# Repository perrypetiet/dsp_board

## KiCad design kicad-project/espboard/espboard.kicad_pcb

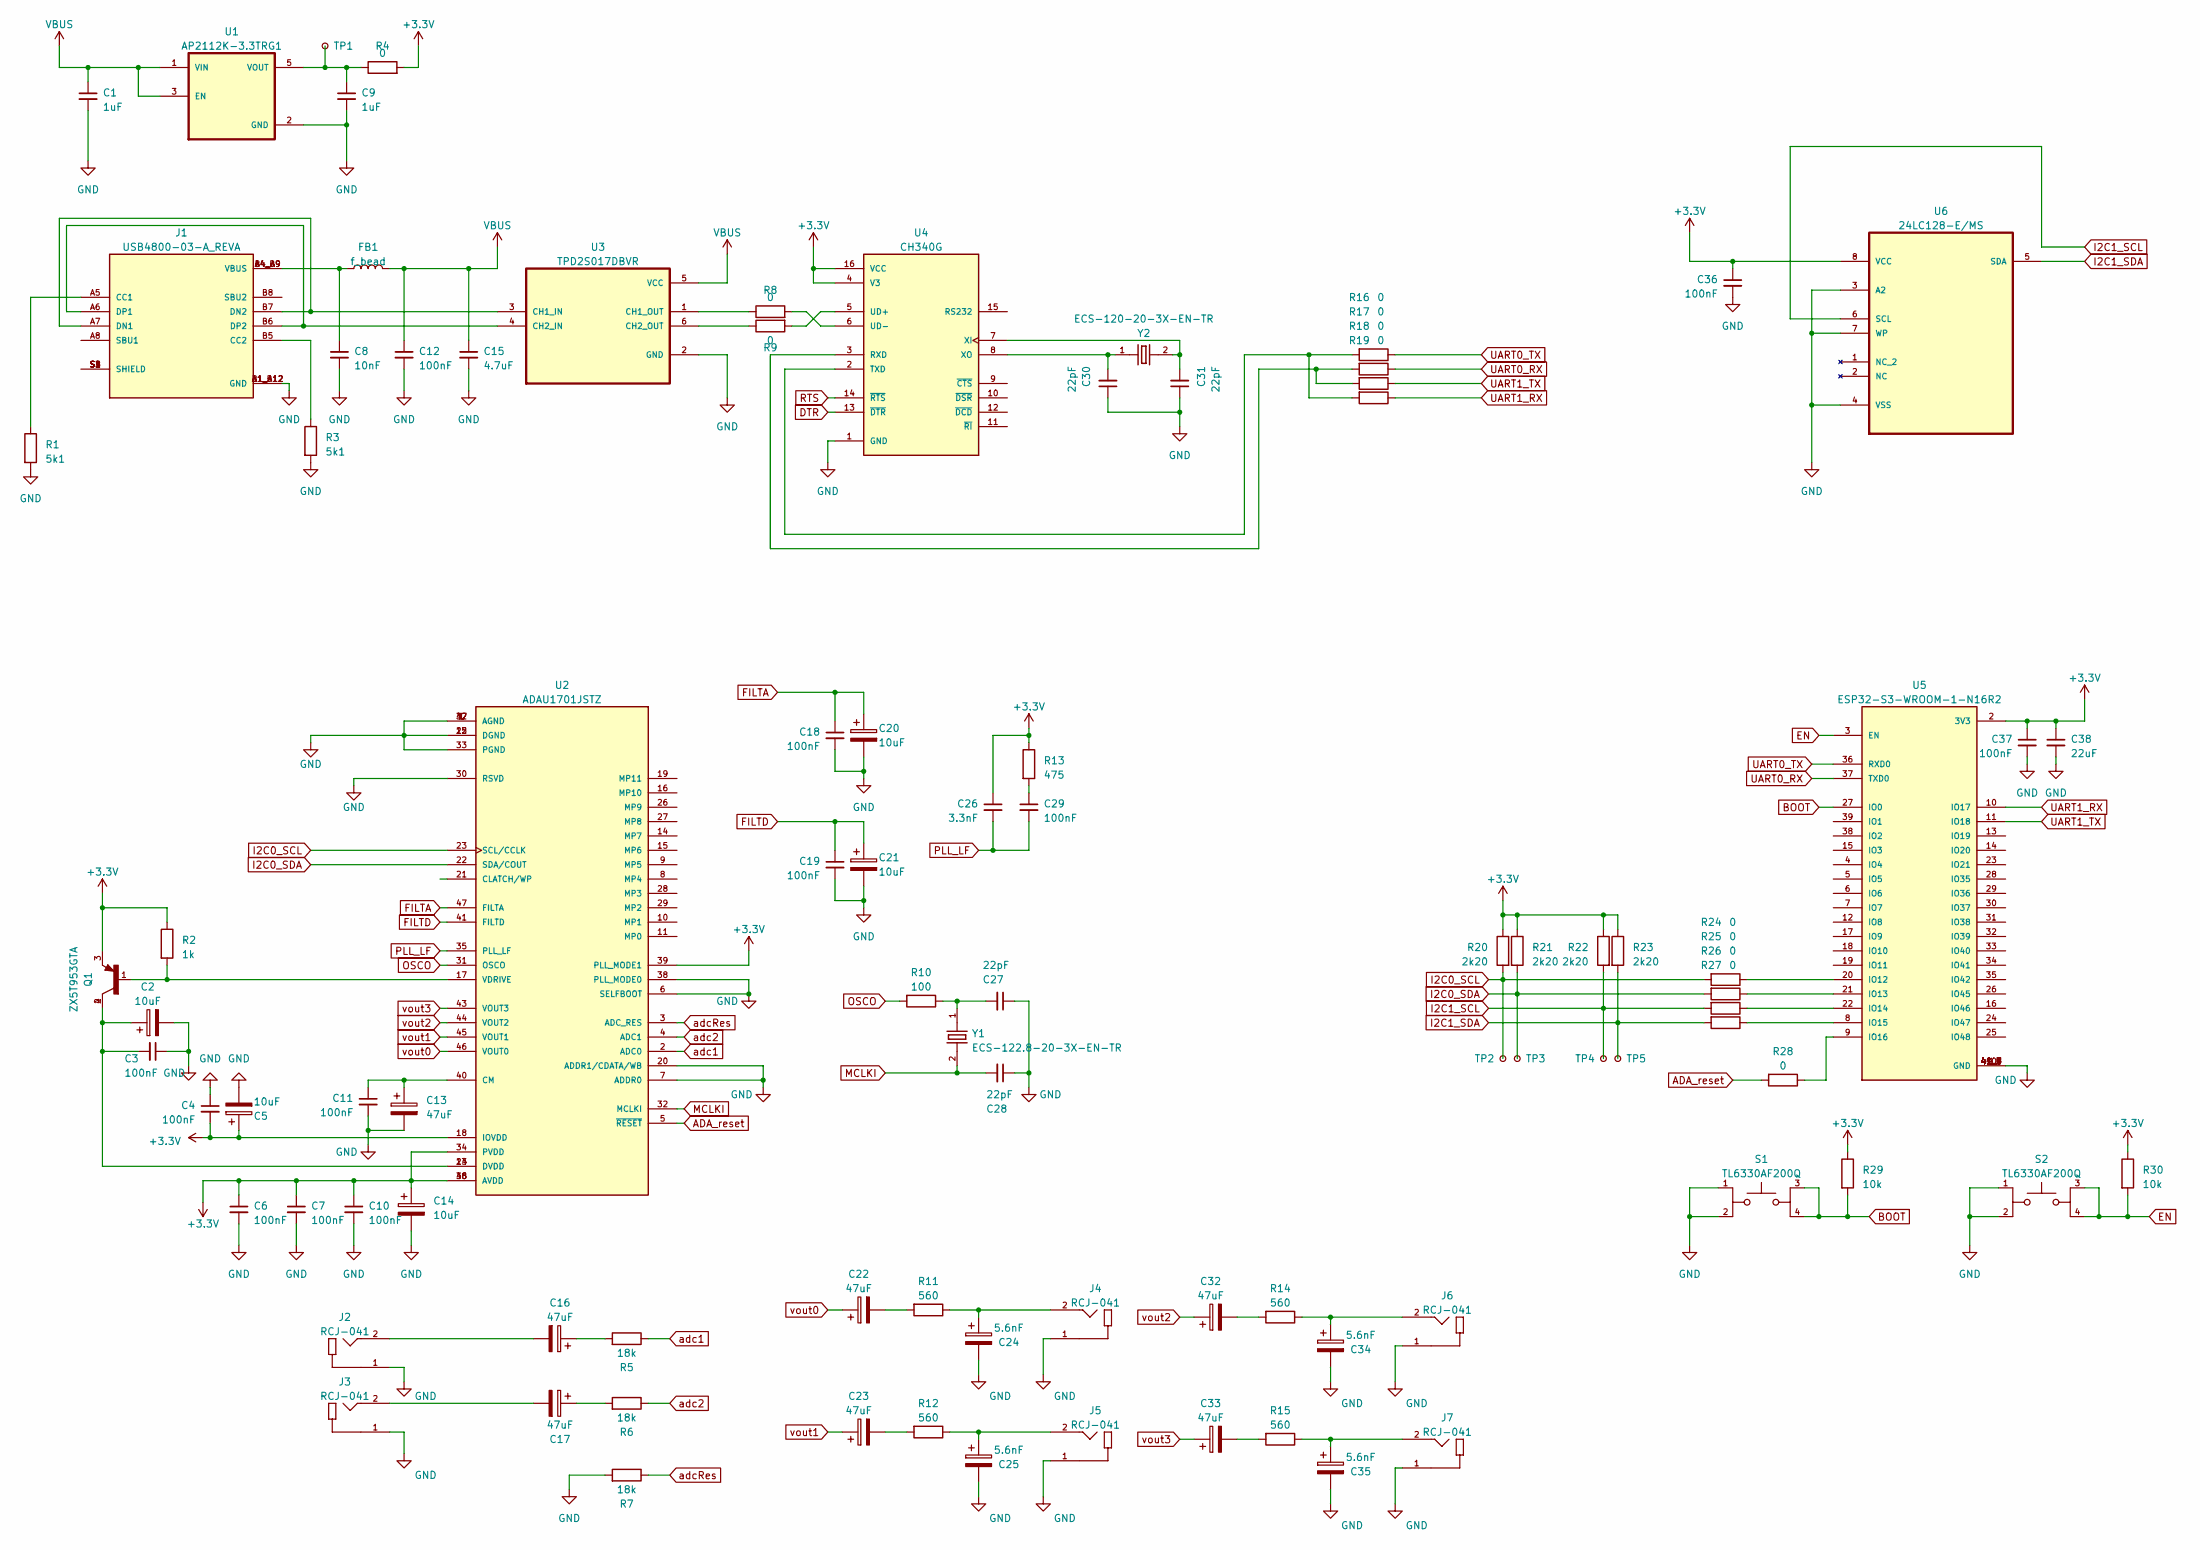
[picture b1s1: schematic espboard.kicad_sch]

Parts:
C1, C9: 1uF; C_0603_1608Metric
C2, C5, C14, C20, C21: 10uF; CP_EIA-1608-08_AVX-J
C3, C4, C6, C7, C10, C11, C12, C18, C19, C29, C36, C37: 100nF; C_0603_1608Metric
C8: 10nF; C_0603_1608Metric
C13, C16, C17: 47uF; CP_EIA-1608-08_AVX-J
C15: 4.7uF; C_0603_1608Metric
C22, C23, C32, C33: 47uF; CP_Elec_5x4.5
C24, C25, C34, C35: 5.6nF; CP_EIA-1608-08_AVX-J
C26: 3.3nF; C_0603_1608Metric
C27, C28, C30, C31: 22pF; C_0603_1608Metric
C38: 22uF; C_0603_1608Metric
FB1: f_bead; L_0805_2012Metric
J1: USB4800-03-A_REVA; GCT_USB4800-03-A_REVA; PARTREV A
J2, J3, J4, J5, J6, J7: RCJ-041; CUI_RCJ-041
Q1: ZX5T953GTA; SOT230P700X180-4N; PARTREV 5-2
R1, R3: 5k1; R_0603_1608Metric
R2: 1k; R_0603_1608Metric
R4, R8, R9, R24, R25, R26, R27, R28: 0; R_0603_1608Metric
R5, R6, R7: 18k; R_0603_1608Metric
R10: 100; R_0603_1608Metric
R11, R12, R14, R15: 560; R_0603_1608Metric
R13: 475; R_0603_1608Metric
R16, R17, R18, R19: 0; R_1206_3216Metric
R20, R21, R22, R23: 2k20; R_0603_1608Metric
R29, R30: 10k; R_0603_1608Metric
S1, S2: TL6330AF200Q; SW_TL6330AF200Q; PARTREV D
TP1: TestPoint_Small; TestPoint_Pad_1.5x1.5mm
TP2, TP3, TP4, TP5: TestPoint_Small; TestPoint_Loop_D2.60mm_Drill1.4mm_Beaded
U1: AP2112K-3.3TRG1; SOT95P285X140-5N; PARTREV 2-2
U2: ADAU1701JSTZ; QFP50P900X900X160-48N; PARTREV C
U3: TPD2S017DBVR; SOT95P280X145-6N
U4: CH340G; SOIC127P600X180-16N; PARTREV 2G
U5: ESP32-S3-WROOM-1-N16R2; XCVR_ESP32-S3-WROOM-1-N16R2; PARTREV v1.0
U6: 24LC128-E/MS; SOP65P490X110-8N; MPN 24LC128-E/MS
Y1: ECS-122.8-20-3X-EN-TR; XTAL_ECS-122.8-20-3X-EN-TR; PARTREV 2017
Y2: ECS-120-20-3X-EN-TR; XTAL_ECS-120-20-3X-EN-TR; PARTREV 2017

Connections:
+3.3V: C4.2, C5.1, C6.1, C7.1, C10.1, C14.1, C26.1, C36.1, C37.1, C38.1, Q1.3, R2.1, R4.2, R13.1, R20.1, R21.1, R22.1, R23.1, R29.1, R30.1, U2.18 (IOVDD), U2.34 (PVDD), U2.36 (AVDD), U2.39 (PLL_MODE1), U2.48 (AVDD), U4.4 (V3), U4.16 (VCC), U5.2 (3V3), U6.8 (VCC)
ADA_reset: R28.2, U2.5 (~RESET)
BOOT: R29.2, S1.3, S1.4, U5.27 (IO0)
DTR: U4.13 (~DTR)
EN: R30.2, S2.3, S2.4, U5.3 (EN)
FILTA: C18.1, C20.1, U2.47 (FILTA)
FILTD: C19.1, C21.1, U2.41 (FILTD)
GND: C1.2, C2.2, C3.1, C4.1, C5.2, C6.2, C7.2, C8.2, C9.2, C10.2, C11.2, C12.2, C13.2, C14.2, C15.2, C18.2, C19.2, C20.2, C21.2, C24.2, C25.2, C27.1, C28.1, C30.1, C31.1, C34.2, C35.2, C36.2, C37.2, C38.2, J1.A1_B12 (GND), J1.B1_A12 (GND), J2.1, J3.1, J4.1, J5.1, J6.1, J7.1, R1.2, R3.2, R7.2, S1.1, S1.2, S2.1, S2.2, U1.2 (GND), U2.1 (AGND), U2.6 (SELFBOOT), U2.7 (ADDR0), U2.12 (DGND), U2.20 (ADDR1/CDATA/WB), U2.25 (DGND), U2.30 (RSVD), U2.33 (PGND), U2.37 (AGND), U2.38 (PLL_MODE0), U2.42 (AGND), U3.2 (GND), U4.1 (GND), U5.1 (GND), U5.40 (GND), U5.41_1 (GND), U5.41_2 (GND), U5.41_3 (GND), U5.41_4 (GND), U5.41_5 (GND), U5.41_6 (GND), U5.41_7 (GND), U5.41_8 (GND), U5.41_9 (GND), U6.3 (A2), U6.4 (VSS), U6.7 (WP)
I2C0_SCL: R20.2, R24.2, TP2.1, U2.23 (SCL/CCLK)
I2C0_SDA: R21.2, R25.2, TP3.1, U2.22 (SDA/COUT)
I2C1_SCL: R22.2, R26.2, TP4.1, U6.6 (SCL)
I2C1_SDA: R23.2, R27.2, TP5.1, U6.5 (SDA)
MCLKI: C28.2, U2.32 (MCLKI), Y1.2
unnamed: C2.1, C3.2, Q1.2, Q1.4, U2.13 (DVDD), U2.24 (DVDD)
unnamed: C8.1, FB1.1, J1.A4_B9 (VBUS), J1.B4_A9 (VBUS)
unnamed: C16.1, R5.2
unnamed: C16.2, J2.2
unnamed: C17.1, R6.2
unnamed: C17.2, J3.2
unnamed: C22.2, R11.2
unnamed: C23.2, R12.2
unnamed: C24.1, J4.2, R11.1
unnamed: C25.1, J5.2, R12.1
unnamed: C27.2, R10.1, Y1.1
unnamed: C29.1, R13.2
unnamed: C32.2, R14.2
unnamed: C33.2, R15.2
unnamed: C34.1, J6.2, R14.1
unnamed: C35.1, J7.2, R15.1
unnamed: J1.A5 (CC1), R1.1
unnamed: J1.B5 (CC2), R3.1
unnamed: J1.A7 (DN1), J1.B7 (DN2), U3.3 (CH1_IN)
unnamed: J1.A6 (DP1), J1.B6 (DP2), U3.4 (CH2_IN)
unnamed: J1.S1 (SHIELD), J1.S2 (SHIELD), J1.S3 (SHIELD), J1.S4 (SHIELD)
unnamed: C9.1, R4.1, TP1.1, U1.5 (VOUT)
unnamed: C11.1, C13.1, U2.40 (CM)
unnamed: Q1.1, R2.2, U2.17 (VDRIVE)
unnamed: R8.1, U3.1 (CH1_OUT)
unnamed: R9.1, U3.6 (CH2_OUT)
unnamed: R17.2, R18.2, U4.3 (RXD)
unnamed: R16.2, R19.2, U4.2 (TXD)
unnamed: R9.2, U4.5 (UD+)
unnamed: R8.2, U4.6 (UD-)
unnamed: C31.2, U4.7 (XI), Y2.2
unnamed: C30.2, U4.8 (XO), Y2.1
unnamed: R24.1, U5.20 (IO12)
unnamed: R25.1, U5.21 (IO13)
unnamed: R26.1, U5.22 (IO14)
unnamed: R27.1, U5.8 (IO15)
unnamed: R28.1, U5.9 (IO16)
OSCO: R10.2, U2.31 (OSCO)
PLL_LF: C26.2, C29.2, U2.35 (PLL_LF)
RTS: U4.14 (~RTS)
UART0_RX: R17.1, U5.37 (TXD0)
UART0_TX: R16.1, U5.36 (RXD0)
UART1_RX: R19.1, U5.10 (IO17)
UART1_TX: R18.1, U5.11 (IO18)
VBUS: C1.1, C12.1, C15.1, FB1.2, U1.1 (VIN), U1.3 (EN), U3.5 (VCC)
adc1: R5.1, U2.2 (ADC0)
adc2: R6.1, U2.4 (ADC1)
adcRes: R7.1, U2.3 (ADC_RES)
vout0: C22.1, U2.46 (VOUT0)
vout1: C23.1, U2.45 (VOUT1)
vout2: C32.1, U2.44 (VOUT2)
vout3: C33.1, U2.43 (VOUT3)

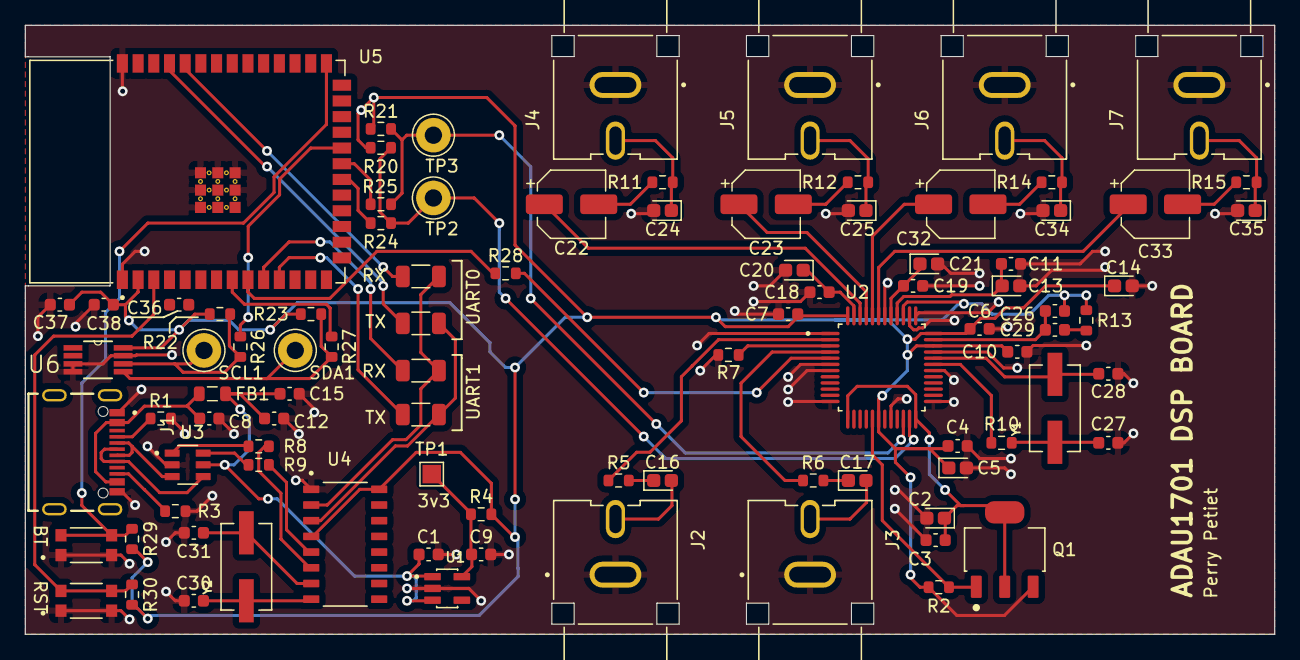
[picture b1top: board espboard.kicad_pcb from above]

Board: 2 copper layers, 101.1 x 49.3 mm, 92 parts (0 on the bottom side), 63 nets.
